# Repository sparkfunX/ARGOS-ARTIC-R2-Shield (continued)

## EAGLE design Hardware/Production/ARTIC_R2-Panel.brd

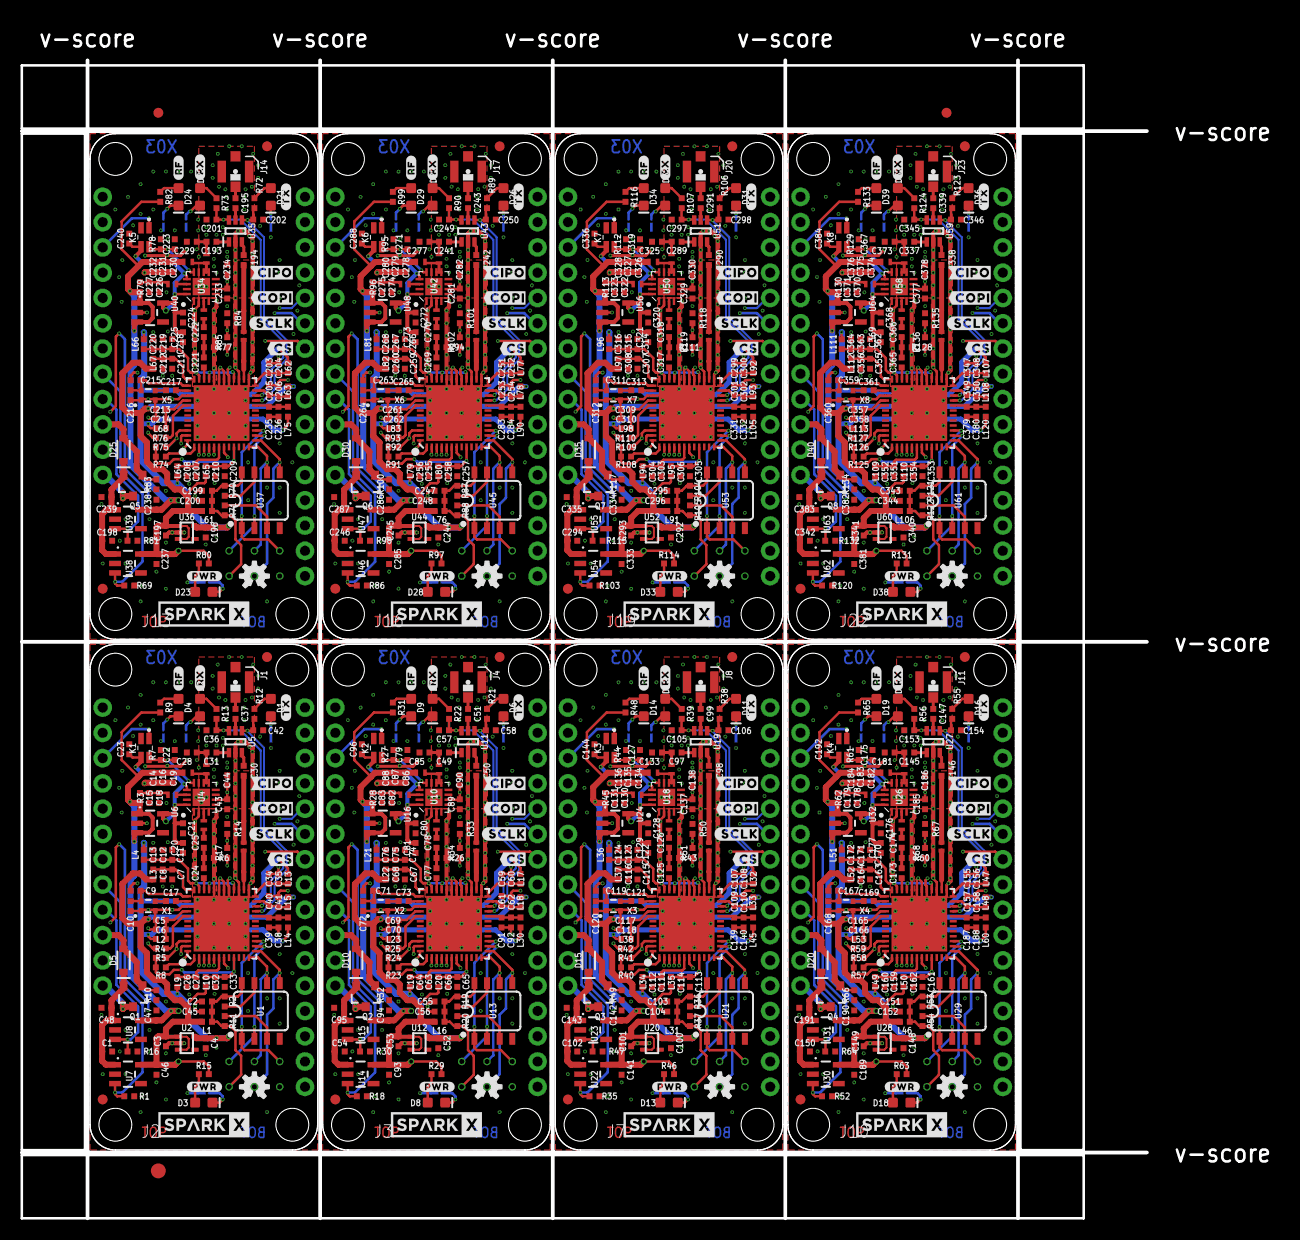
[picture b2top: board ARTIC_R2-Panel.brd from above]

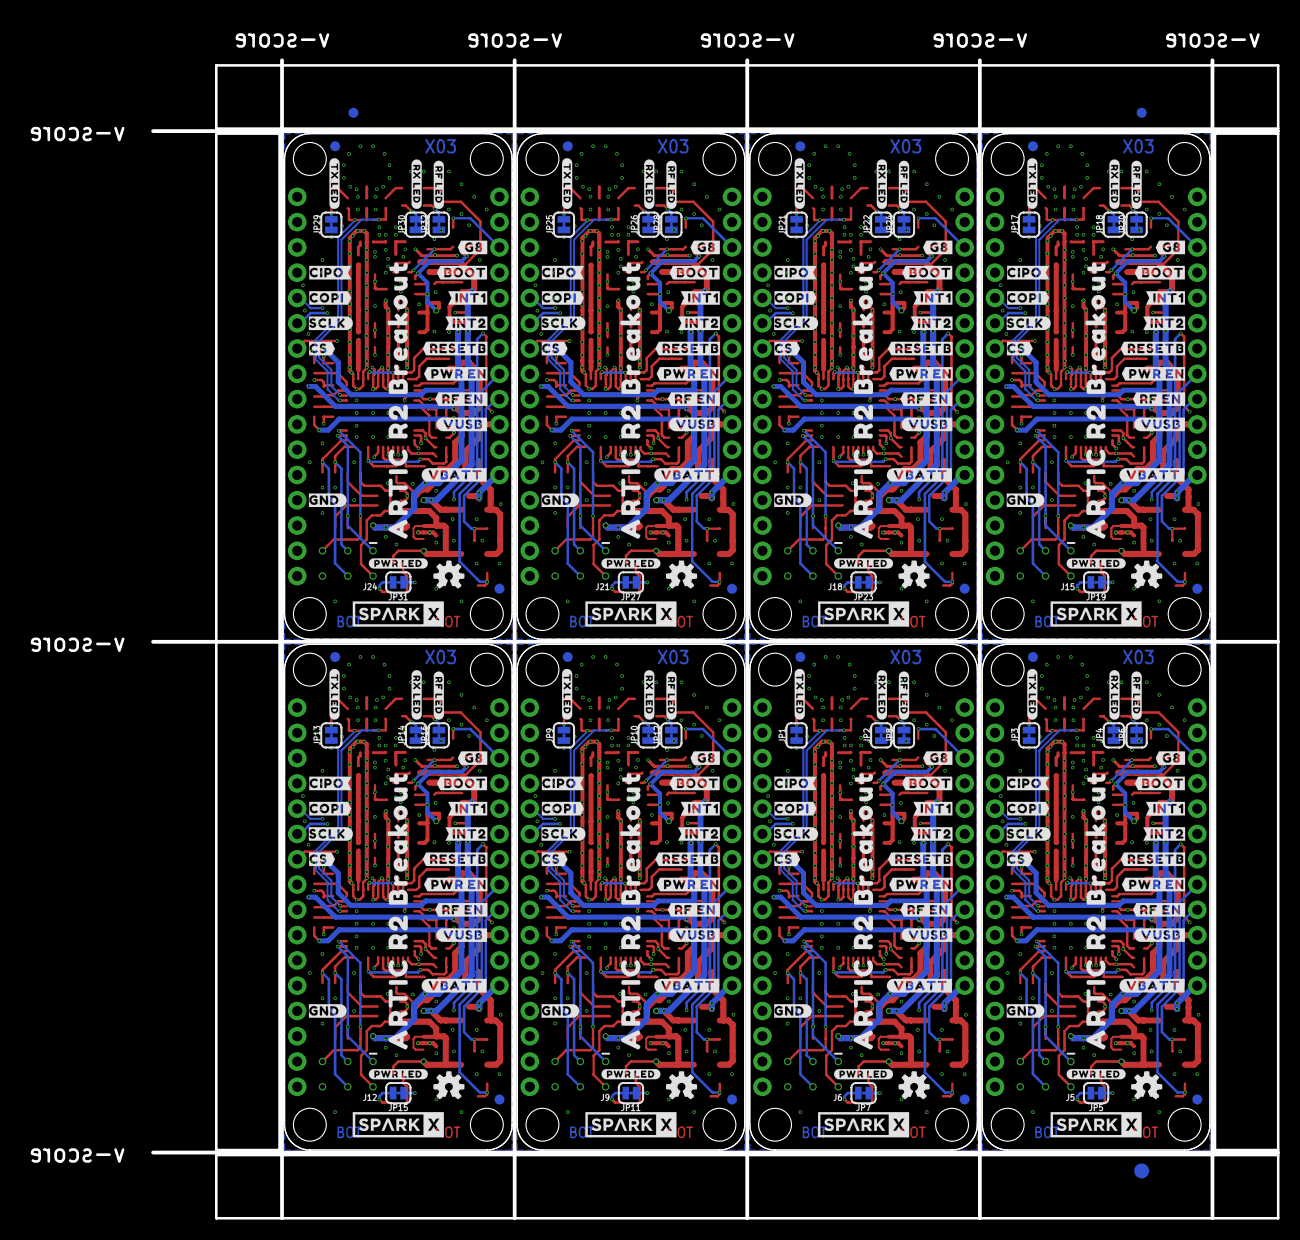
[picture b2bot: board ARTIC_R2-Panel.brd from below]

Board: 4 copper layers, 113.0 x 116.3 mm, 1142 parts (227 on the bottom side), 520 nets.

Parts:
C1, C15, C16, C20, C44, C46, C47, C54, C81, C83, C87, C90, C93, C94, C102, C129, C131, C135, C138, C141, C142, C150, C177, C179, C183, C186, C189, C190, C198, C225, C227, C231, C234, C237, C238, C246, C273, C275, C279, C282, C285, C286, C294, C321, C323, C327, C330, C333, C334, C342, C369, C371, C375, C378, C381, C382: 2.2uF; 0402-TIGHT
C2, C5, C7, C18, C27, C33, C34, C39, C40, C55, C59, C61, C63, C65, C67, C69, C82, C91, C103, C107, C109, C111, C113, C115, C117, C130, C139, C151, C155, C157, C159, C161, C163, C165, C178, C187, C199, C203, C205, C207, C209, C211, C213, C226, C235, C247, C251, C253, C255, C257, C259, C261, C274, C283, C295, C299, C301, C303, C305, C307, C309, C322, C331, C343, C347, C349, C351, C353, C355, C357, C370, C379: 22pF; 0402-TIGHT
C3, C4, C9, C12, C52, C53, C71, C75, C100, C101, C119, C123, C148, C149, C167, C171, C196, C197, C215, C219, C244, C245, C263, C267, C292, C293, C311, C315, C340, C341, C359, C363: 1.0uF; 0402-TIGHT
C6, C8, C26, C32, C35, C38, C41, C45, C48, C56, C60, C62, C64, C66, C68, C70, C92, C95, C104, C108, C110, C112, C114, C116, C118, C140, C143, C152, C156, C158, C160, C162, C164, C166, C188, C191, C200, C204, C206, C208, C210, C212, C214, C236, C239, C248, C252, C254, C256, C258, C260, C262, C284, C287, C296, C300, C302, C304, C306, C308, C310, C332, C335, C344, C348, C350, C352, C354, C356, C358, C380, C383: 0.1uF; 0402-TIGHT
C10, C72, C120, C168, C216, C264, C312, C360: 47nF; 0402-TIGHT
C11, C19, C21, C22, C23, C24, C25, C30, C31, C36, C37, C42, C43, C49, C50, C51, C57, C58, C74, C77, C78, C79, C80, C86, C89, C96, C97, C98, C99, C105, C106, C122, C125, C126, C127, C128, C134, C137, C144, C145, C146, C147, C153, C154, C170, C173, C174, C175, C176, C182, C185, C192, C193, C194, C195, C201, C202, C218, C221, C222, C223, C224, C230, C233, C240, C241, C242, C243, C249, C250, C266, C269, C270, C271, C272, C278, C281, C288, C289, C290, C291, C297, C298, C314, C317, C318, C319, C320, C326, C329, C336, C337, C338, C339, C345, C346, C362, C365, C366, C367, C368, C374, C377, C384: 100pF; 0402-TIGHT
C13, C14, C76, C88, C124, C136, C172, C184, C220, C232, C268, C280, C316, C328, C364, C376: 10uF; 0402-TIGHT
C17, C73, C121, C169, C217, C265, C313, C361: 1.0nF; 0402-TIGHT
C28, C85, C133, C181, C229, C277, C325, C373: 9.1pF; 0402-TIGHT
C29, C84, C132, C180, C228, C276, C324, C372: 2.4 pF; 0402_MURATA
D1, D2, D6, D7, D11, D12, D16, D17, D21, D22, D26, D27, D31, D32, D36, D37: Yellow; LED-0603
D3, D4, D8, D9, D13, D14, D18, D19, D23, D24, D28, D29, D33, D34, D38, D39: RED; LED-0603
D5, D10, D15, D20, D25, D30, D35, D40: 1A/23V/620mV; SOD-323
E$1, E$2, E$3, E$4: FIDUCIAL-1X2
E$5, E$6: FIDUCIAL-1.5X3
FD1, FD2, FD3, FD4, FD5, FD6, FD7, FD8, FD9, FD10, FD11, FD12, FD13, FD14, FD15, FD16, FD17, FD18, FD19, FD20, FD21, FD22, FD23, FD24, FD25, FD26, FD27, FD28, FD29, FD30, FD31, FD32: FIDUCIAL1X2; FIDUCIAL-1X2
J1, J4, J8, J11, J14, J17, J20, J23: U.FL
J2, J3, J7, J10, J13, J16, J19, J22: THING_PLUS
J5, J6, J9, J12, J15, J18, J21, J24: Flash Programming; 2X3_TEST_POINTS
JP1, JP2, JP3, JP4, JP5, JP6, JP7, JP8, JP9, JP10, JP11, JP12, JP13, JP14, JP15, JP16, JP17, JP18, JP19, JP20, JP21, JP22, JP23, JP24, JP25, JP26, JP27, JP28, JP29, JP30, JP31, JP32: JUMPER-SMT_2_NC_TRACE_SILK; SMT-JUMPER_2_NC_TRACE_SILK
K1, K2, K3, K4, K5, K6, K7, K8: TLP3475R; TLP3475RTPF
L1, L2, L3, L4, L9, L10, L13, L14, L15, L16, L17, L18, L19, L20, L21, L22, L23, L30, L31, L32, L33, L34, L35, L36, L37, L38, L45, L46, L47, L48, L49, L50, L51, L52, L53, L60, L61, L62, L63, L64, L65, L66, L67, L68, L75, L76, L77, L78, L79, L80, L81, L82, L83, L90, L91, L92, L93, L94, L95, L96, L97, L98, L105, L106, L107, L108, L109, L110, L111, L112, L113, L120: 30Ω; 0402-TIGHT
L5, L25, L40, L55, L70, L85, L100, L115: 15nH; 0402_COILCRAFT
L6, L26, L41, L56, L71, L86, L101, L116: 27nH; 0402_COILCRAFT
L7, L24, L39, L54, L69, L84, L99, L114: 18nH; 0402_COILCRAFT
L8, L27, L42, L57, L72, L87, L102, L117: 12nH; 0402_COILCRAFT
L11, L28, L43, L58, L73, L88, L103, L118: 30nH; 0402_COILCRAFT
L12, L29, L44, L59, L74, L89, L104, L119: 51nH; 0402_COILCRAFT
LOGO1, LOGO2, LOGO3, LOGO4, LOGO5, LOGO6, LOGO7, LOGO8, LOGO9, LOGO10, LOGO11, LOGO12, LOGO13, LOGO14, LOGO15, LOGO16: OSHW-LOGOS; OSHW-LOGO-S
Q1, Q2, Q3, Q4, Q5, Q6, Q7, Q8: 3.1A/30V/105mΩ; SOT23-3
R1, R7, R16, R18, R27, R30, R35, R44, R47, R52, R61, R64, R69, R78, R81, R86, R95, R98, R103, R112, R115, R120, R129, R132: 10k; 0402-TIGHT
R2, R11, R19, R20, R36, R37, R53, R54, R70, R71, R87, R88, R104, R105, R121, R122: 0; 0402-TIGHT
R3, R28, R45, R62, R79, R96, R113, R130: 3.9OHM; 0402-TIGHT
R4, R25, R42, R59, R76, R93, R110, R127: 33k; 0402-TIGHT
R5, R8, R10, R23, R24, R32, R40, R41, R49, R57, R58, R66, R74, R75, R83, R91, R92, R100, R108, R109, R117, R125, R126, R134: 100k; 0402-TIGHT
R6, R26, R43, R60, R77, R94, R111, R128: 220OHM; 0402-TIGHT
R9, R12, R13, R15, R21, R22, R29, R31, R38, R39, R46, R48, R55, R56, R63, R65, R72, R73, R80, R82, R89, R90, R97, R99, R106, R107, R114, R116, R123, R124, R131, R133: 1k; 0402-TIGHT
R14, R33, R50, R67, R84, R101, R118, R135: 470; 0402-TIGHT
R17, R34, R51, R68, R85, R102, R119, R136: 47; 0402-TIGHT
SPARKX1, SPARKX2, SPARKX3, SPARKX4, SPARKX5, SPARKX6, SPARKX7, SPARKX8, SPARKX9, SPARKX10, SPARKX11, SPARKX12, SPARKX13, SPARKX14, SPARKX15, SPARKX16: SPARKX-LOGO4; SPARKX-MEDIUM
TP1, TP2, TP3, TP4, TP5, TP6, TP7, TP8, TP9, TP10, TP11, TP12, TP13, TP14, TP15, TP16, TP17, TP18, TP19, TP20, TP21, TP22, TP23, TP24, TP25, TP26, TP27, TP28, TP29, TP30, TP31, TP32: TEST-POINTTP_15TH_THRU; TP_15TH
U1, U13, U21, U29, U37, U45, U53, U61: 2Mbit SPI Flash; SO08
U2, U12, U20, U28, U36, U44, U52, U60: 1.8V/100mA; SC70
U3, U9, U17, U25, U33, U41, U49, U57: ARTIC_R2; QFN-48
U4, U10, U18, U26, U34, U42, U50, U58: RFPA0133; QFN50P300X300X86-17N
U5, U11, U19, U27, U35, U43, U51, U59: AS179-92LF; SOT65P220X100-6N
U6, U16, U24, U32, U40, U48, U56, U64: 3.0V; SOT23-5
U7, U8, U14, U15, U22, U23, U30, U31, U38, U39, U46, U47, U54, U55, U62, U63: 3.3V; SOT23-5
U$1, U$30, U$57, U$84, U$111, U$138, U$165, U$192: #TX#0
U$2, U$31, U$58, U$85, U$112, U$139, U$166, U$193: #RX#0
U$3, U$22, U$55, U$82, U$109, U$136, U$163, U$190: #RX_LED#0
U$4, U$23, U$56, U$83, U$110, U$137, U$164, U$191: #TX_LED#0
U$5, U$49, U$76, U$103, U$130, U$157, U$184, U$211: #RF_LED#0
U$6, U$54, U$81, U$108, U$135, U$162, U$189, U$216: #G8#0
U$7, U$50, U$77, U$104, U$131, U$158, U$185, U$212: #RF#0
U$8, U$51, U$78, U$105, U$132, U$159, U$186, U$213: #RF_EN#0
U$9, U$32, U$59, U$86, U$113, U$140, U$167, U$194: CIPO#0
U$10, U$33, U$60, U$87, U$114, U$141, U$168, U$195: #CIPO0
U$11, U$34, U$61, U$88, U$115, U$142, U$169, U$196: #COPI0
U$12, U$35, U$62, U$89, U$116, U$143, U$170, U$197: COPI#0
U$13, U$36, U$63, U$90, U$117, U$144, U$171, U$198: #SCLK0
U$14, U$37, U$64, U$91, U$118, U$145, U$172, U$199: SCLK#0
U$15, U$38, U$65, U$92, U$119, U$146, U$173, U$200: #CS0
U$16, U$39, U$66, U$93, U$120, U$147, U$174, U$201: CS#0
U$17, U$43, U$70, U$97, U$124, U$151, U$178, U$205: GND#0
U$18, U$41, U$68, U$95, U$122, U$149, U$176, U$203: #RESETB0
U$19, U$42, U$69, U$96, U$123, U$150, U$177, U$204: #PWR_EN0
U$20, U$52, U$79, U$106, U$133, U$160, U$187, U$214: #VBATT#0
U$21, U$53, U$80, U$107, U$134, U$161, U$188, U$215: #VUSB#0
U$24, U$40, U$67, U$94, U$121, U$148, U$175, U$202: #BOOT0
U$25, U$45, U$72, U$99, U$126, U$153, U$180, U$207: #INT10
U$26, U$44, U$71, U$98, U$125, U$152, U$179, U$206: #INT20
U$27, U$46, U$73, U$100, U$127, U$154, U$181, U$208: #PWR_LED#0
U$28, U$47, U$74, U$101, U$128, U$155, U$182, U$209: #PWR#0
U$29, U$48, U$75, U$102, U$129, U$156, U$183, U$210: ARTIC_R2_BREAKOUT0
X1, X2, X3, X4, X5, X6, X7, X8: CRYSTAL-TCXO-26MHZ; CRYSTAL-TCXO-SMD-1.65X1.25

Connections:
1.8V: C4.1, L2.2, L4.2, L9.2, L13.2, L14.2, TP3.P$1, U2.5
1.8V1: C52.1, L17.2, L19.2, L21.2, L23.2, L30.2, TP7.P$1, U12.5
1.8V2: C100.1, L32.2, L34.2, L36.2, L38.2, L45.2, TP11.P$1, U20.5
1.8V3: C148.1, L47.2, L49.2, L51.2, L53.2, L60.2, TP15.P$1, U28.5
1.8V4: C196.1, L62.2, L64.2, L66.2, L68.2, L75.2, TP19.P$1, U36.5
1.8V5: C244.1, L77.2, L79.2, L81.2, L83.2, L90.2, TP23.P$1, U44.5
1.8V6: C292.1, L92.2, L94.2, L96.2, L98.2, L105.2, TP27.P$1, U52.5
1.8V7: C340.1, L107.2, L109.2, L111.2, L113.2, L120.2, TP31.P$1, U60.5
ANTENNA: C37.1, J1.FEED
ANTENNA1: C51.1, J4.FEED
ANTENNA2: C99.1, J8.FEED
ANTENNA3: C147.1, J11.FEED
ANTENNA4: C195.1, J14.FEED
ANTENNA5: C243.1, J17.FEED
ANTENNA6: C291.1, J20.FEED
ANTENNA7: C339.1, J23.FEED
ARTIC_PWR_EN: J2.8, R1.2, U7.3
ARTIC_PWR_EN1: J3.8, R18.2, U14.3
ARTIC_PWR_EN2: J7.8, R35.2, U22.3
ARTIC_PWR_EN3: J10.8, R52.2, U30.3
ARTIC_PWR_EN4: J13.8, R69.2, U38.3
ARTIC_PWR_EN5: J16.8, R86.2, U46.3
ARTIC_PWR_EN6: J19.8, R103.2, U54.3
ARTIC_PWR_EN7: J22.8, R120.2, U62.3
BOOT: J2.4, R5.1, U3.46
BOOT1: J3.4, R24.1, U9.46
BOOT2: J7.4, R41.1, U17.46
BOOT3: J10.4, R58.1, U25.46
BOOT4: J13.4, R75.1, U33.46
BOOT5: J16.4, R92.1, U41.46
BOOT6: J19.4, R109.1, U49.46
BOOT7: J22.4, R126.1, U57.46
CIPO: J2.16, U3.5
CIPO1: J3.16, U9.5
CIPO2: J7.16, U17.5
CIPO3: J10.16, U25.5
CIPO4: J13.16, U33.5
CIPO5: J16.16, U41.5
CIPO6: J19.16, U49.5
CIPO7: J22.16, U57.5
COPI: J2.17, U3.4
COPI1: J3.17, U9.4
COPI2: J7.17, U17.4
COPI3: J10.17, U25.4
COPI4: J13.17, U33.4
COPI5: J16.17, U41.4
COPI6: J19.17, U49.4
COPI7: J22.17, U57.4
CS: J2.19, U3.2
CS1: J3.19, U9.2
CS2: J7.19, U17.2
CS3: J10.19, U25.2
CS4: J13.19, U33.2
CS5: J16.19, U41.2
CS6: J19.19, U49.2
CS7: J22.19, U57.2
FLSH_CEN: J5.5, U1.1, U3.15
FLSH_CEN1: J6.5, U9.15, U13.1
FLSH_CEN2: J9.5, U17.15, U21.1
FLSH_CEN3: J12.5, U25.15, U29.1
FLSH_CEN4: J15.5, U33.15, U37.1
FLSH_CEN5: J18.5, U41.15, U45.1
FLSH_CEN6: J21.5, U49.15, U53.1
FLSH_CEN7: J24.5, U57.15, U61.1
FLSH_SCLK: J5.3, U1.6, U3.12
FLSH_SCLK1: J6.3, U9.12, U13.6
FLSH_SCLK2: J9.3, U17.12, U21.6
FLSH_SCLK3: J12.3, U25.12, U29.6
FLSH_SCLK4: J15.3, U33.12, U37.6
FLSH_SCLK5: J18.3, U41.12, U45.6
FLSH_SCLK6: J21.3, U49.12, U53.6
FLSH_SCLK7: J24.3, U57.12, U61.6
FLSH_SI: J5.4, U1.5, U3.13
FLSH_SI1: J6.4, U9.13, U13.5
FLSH_SI2: J9.4, U17.13, U21.5
FLSH_SI3: J12.4, U25.13, U29.5
FLSH_SI4: J15.4, U33.13, U37.5
FLSH_SI5: J18.4, U41.13, U45.5
FLSH_SI6: J21.4, U49.13, U53.5
FLSH_SI7: J24.4, U57.13, U61.5
FLSH_SO: J5.1, U1.2, U3.14
FLSH_SO1: J6.1, U9.14, U13.2
FLSH_SO2: J9.1, U17.14, U21.2
FLSH_SO3: J12.1, U25.14, U29.2
FLSH_SO4: J15.1, U33.14, U37.2
FLSH_SO5: J18.1, U41.14, U45.2
FLSH_SO6: J21.1, U49.14, U53.2
FLSH_SO7: J24.1, U57.14, U61.2
FLSH_VCC: C2.1, C45.1, J5.2, L1.1, R2.2, R11.2, U1.8
FLSH_VCC1: C55.1, C56.1, J6.2, L16.1, R19.2, R20.2, U13.8
FLSH_VCC2: C103.1, C104.1, J9.2, L31.1, R36.2, R37.2, U21.8
FLSH_VCC3: C151.1, C152.1, J12.2, L46.1, R53.2, R54.2, U29.8
FLSH_VCC4: C199.1, C200.1, J15.2, L61.1, R70.2, R71.2, U37.8
FLSH_VCC5: C247.1, C248.1, J18.2, L76.1, R87.2, R88.2, U45.8
FLSH_VCC6: C295.1, C296.1, J21.2, L91.1, R104.2, R105.2, U53.8
FLSH_VCC7: C343.1, C344.1, J24.2, L106.1, R121.2, R122.2, U61.8
G1: J3.3, K2.1
G2: J7.3, K3.1
G3: J10.3, K4.1
G4: J13.3, K5.1
G5: J16.3, K6.1
G6: J19.3, K7.1
G7: J22.3, K8.1
G8: J2.3, K1.1
GND: C1.2, C2.2, C3.2, C4.2, C5.2, C6.2, C7.2, C8.2, C9.2, C10.2, C11.2, C12.2, C13.2, C14.2, C15.2, C16.2, C18.2, C19.2, C20.1, C21.1, C22.1, C23.2, C26.2, C27.2, C28.1, C32.2, C33.2, C34.2, C35.2, C36.2, C38.2, C39.2, C40.2, C41.2, C42.2, C43.1, C44.2, C45.2, C46.2, C47.2, C48.2, J1.1, J1.2, J2.25, J5.6, JP3.1, JP4.1, JP5.1, JP6.1, K1.2, L11.P$1, L12.P$1, R1.1, R4.2, R6.1, R7.2, R10.1, R14.1, R16.1, U1.4, U2.2, U3.25, U3.27, U3.29, U3.30, U3.31, U3.32, U3.39, U3.GND, U4.2, U4.EDAP, U5.2, U6.2, U7.2, U8.2, X1.1, X1.2
GND1: C52.2, C53.2, C54.2, C55.2, C56.2, C57.2, C58.2, C59.2, C60.2, C61.2, C62.2, C63.2, C64.2, C65.2, C66.2, C67.2, C68.2, C69.2, C70.2, C71.2, C72.2, C74.2, C75.2, C76.2, C79.1, C80.1, C81.1, C82.2, C83.2, C85.1, C86.2, C87.2, C88.2, C89.1, C90.2, C91.2, C92.2, C93.2, C94.2, C95.2, C96.2, J3.25, J4.1, J4.2, J6.6, JP1.1, JP2.1, JP7.1, JP8.1, K2.2, L28.P$1, L29.P$1, R18.1, R25.2, R26.1, R27.2, R30.1, R32.1, R33.1, U9.25, U9.27, U9.29, U9.30, U9.31, U9.32, U9.39, U9.GND, U10.2, U10.EDAP, U11.2, U12.2, U13.4, U14.2, U15.2, U16.2, X2.1, X2.2
GND2: C100.2, C101.2, C102.2, C103.2, C104.2, C105.2, C106.2, C107.2, C108.2, C109.2, C110.2, C111.2, C112.2, C113.2, C114.2, C115.2, C116.2, C117.2, C118.2, C119.2, C120.2, C122.2, C123.2, C124.2, C127.1, C128.1, C129.1, C130.2, C131.2, C133.1, C134.2, C135.2, C136.2, C137.1, C138.2, C139.2, C140.2, C141.2, C142.2, C143.2, C144.2, J7.25, J8.1, J8.2, J9.6, JP9.1, JP10.1, JP11.1, JP12.1, K3.2, L43.P$1, L44.P$1, R35.1, R42.2, R43.1, R44.2, R47.1, R49.1, R50.1, U17.25, U17.27, U17.29, U17.30, U17.31, U17.32, U17.39, U17.GND, U18.2, U18.EDAP, U19.2, U20.2, U21.4, U22.2, U23.2, U24.2, X3.1, X3.2
GND3: C148.2, C149.2, C150.2, C151.2, C152.2, C153.2, C154.2, C155.2, C156.2, C157.2, C158.2, C159.2, C160.2, C161.2, C162.2, C163.2, C164.2, C165.2, C166.2, C167.2, C168.2, C170.2, C171.2, C172.2, C175.1, C176.1, C177.1, C178.2, C179.2, C181.1, C182.2, C183.2, C184.2, C185.1, C186.2, C187.2, C188.2, C189.2, C190.2, C191.2, C192.2, J10.25, J11.1, J11.2, J12.6, JP13.1, JP14.1, JP15.1, JP16.1, K4.2, L58.P$1, L59.P$1, R52.1, R59.2, R60.1, R61.2, R64.1, R66.1, R67.1, U25.25, U25.27, U25.29, U25.30, U25.31, U25.32, U25.39, U25.GND, U26.2, U26.EDAP, U27.2, U28.2, U29.4, U30.2, U31.2, U32.2, X4.1, X4.2
GND4: C196.2, C197.2, C198.2, C199.2, C200.2, C201.2, C202.2, C203.2, C204.2, C205.2, C206.2, C207.2, C208.2, C209.2, C210.2, C211.2, C212.2, C213.2, C214.2, C215.2, C216.2, C218.2, C219.2, C220.2, C223.1, C224.1, C225.1, C226.2, C227.2, C229.1, C230.2, C231.2, C232.2, C233.1, C234.2, C235.2, C236.2, C237.2, C238.2, C239.2, C240.2, J13.25, J14.1, J14.2, J15.6, JP17.1, JP18.1, JP19.1, JP20.1, K5.2, L73.P$1, L74.P$1, R69.1, R76.2, R77.1, R78.2, R81.1, R83.1, R84.1, U33.25, U33.27, U33.29, U33.30, U33.31, U33.32, U33.39, U33.GND, U34.2, U34.EDAP, U35.2, U36.2, U37.4, U38.2, U39.2, U40.2, X5.1, X5.2
GND5: C244.2, C245.2, C246.2, C247.2, C248.2, C249.2, C250.2, C251.2, C252.2, C253.2, C254.2, C255.2, C256.2, C257.2, C258.2, C259.2, C260.2, C261.2, C262.2, C263.2, C264.2, C266.2, C267.2, C268.2, C271.1, C272.1, C273.1, C274.2, C275.2, C277.1, C278.2, C279.2, C280.2, C281.1, C282.2, C283.2, C284.2, C285.2, C286.2, C287.2, C288.2, J16.25, J17.1, J17.2, J18.6, JP21.1, JP22.1, JP23.1, JP24.1, K6.2, L88.P$1, L89.P$1, R86.1, R93.2, R94.1, R95.2, R98.1, R100.1, R101.1, U41.25, U41.27, U41.29, U41.30, U41.31, U41.32, U41.39, U41.GND, U42.2, U42.EDAP, U43.2, U44.2, U45.4, U46.2, U47.2, U48.2, X6.1, X6.2
GND6: C292.2, C293.2, C294.2, C295.2, C296.2, C297.2, C298.2, C299.2, C300.2, C301.2, C302.2, C303.2, C304.2, C305.2, C306.2, C307.2, C308.2, C309.2, C310.2, C311.2, C312.2, C314.2, C315.2, C316.2, C319.1, C320.1, C321.1, C322.2, C323.2, C325.1, C326.2, C327.2, C328.2, C329.1, C330.2, C331.2, C332.2, C333.2, C334.2, C335.2, C336.2, J19.25, J20.1, J20.2, J21.6, JP25.1, JP26.1, JP27.1, JP28.1, K7.2, L103.P$1, L104.P$1, R103.1, R110.2, R111.1, R112.2, R115.1, R117.1, R118.1, U49.25, U49.27, U49.29, U49.30, U49.31, U49.32, U49.39, U49.GND, U50.2, U50.EDAP, U51.2, U52.2, U53.4, U54.2, U55.2, U56.2, X7.1, X7.2
GND7: C340.2, C341.2, C342.2, C343.2, C344.2, C345.2, C346.2, C347.2, C348.2, C349.2, C350.2, C351.2, C352.2, C353.2, C354.2, C355.2, C356.2, C357.2, C358.2, C359.2, C360.2, C362.2, C363.2, C364.2, C367.1, C368.1, C369.1, C370.2, C371.2, C373.1, C374.2, C375.2, C376.2, C377.1, C378.2, C379.2, C380.2, C381.2, C382.2, C383.2, C384.2, J22.25, J23.1, J23.2, J24.6, JP29.1, JP30.1, JP31.1, JP32.1, K8.2, L118.P$1, L119.P$1, R120.1, R127.2, R128.1, R129.2, R132.1, R134.1, R135.1, U57.25, U57.27, U57.29, U57.30, U57.31, U57.32, U57.39, U57.GND, U58.2, U58.EDAP, U59.2, U60.2, U61.4, U62.2, U63.2, U64.2, X8.1, X8.2
INT1: J2.5, U3.47
INT2: J2.6, U3.48
INT3: J3.6, U9.48
INT4: J3.5, U9.47
INT5: J7.6, U17.48
INT6: J7.5, U17.47
INT7: J10.6, U25.48
INT8: J10.5, U25.47
INT9: J13.6, U33.48
INT10: J13.5, U33.47
INT11: J16.6, U41.48
INT12: J16.5, U41.47
INT13: J19.6, U49.48
INT14: J19.5, U49.47
INT15: J22.6, U57.48
INT16: J22.5, U57.47
unnamed: C49.1, U11.1
unnamed: R2.1, U1.7
unnamed: R11.1, U1.3
unnamed: C34.1, C35.1, L13.1, U3.24
unnamed: C40.1, C41.1, L15.1, U3.23
unnamed: D2.A, R13.1
unnamed: D1.A, R12.1
unnamed: C26.1, C27.1, L9.1, U3.6
unnamed: C32.1, C33.1, L10.1, R5.2, R8.1, U3.9
unnamed: C11.1, C12.1, C13.1, L4.1, U3.28, U3.33, U3.35
unnamed: C7.1, C8.1, L3.1, U3.36
unnamed: R4.1, U3.41
unnamed: C5.1, C6.1, L2.1, U3.40
unnamed: C9.1, C10.1, U3.37, X1.4
unnamed: C17.1, X1.3
unnamed: C17.2, U3.38
unnamed: C24.1, U3.34
unnamed: C24.2, C25.1, R6.2
unnamed: L5.P$2, U4.14
unnamed: C15.1, C18.1, L5.P$1, R3.1
unnamed: C29.P$1, L11.P$2, U3.26
unnamed: D4.A, R9.1
unnamed: C50.1, U11.3
unnamed: C25.2, L7.P$1
unnamed: L7.P$2, U4.3
unnamed: L6.P$2, L8.P$1, U4.9, U4.10
unnamed: D4.C, JP6.2
unnamed: C31.1, U5.1
unnamed: C30.1, U5.3
unnamed: C37.2, U5.5
unnamed: C38.1, C39.1, L14.1, U3.20
unnamed: C51.2, U11.5
unnamed: R19.1, U13.7
unnamed: R20.1, U13.3
unnamed: D1.C, JP3.2
unnamed: D2.C, JP4.2
unnamed: D3.A, R15.1
unnamed: D3.C, JP5.2
unnamed: C59.1, C60.1, L17.1, U9.24
unnamed: C61.1, C62.1, L18.1, U9.23
unnamed: D7.A, R22.1
unnamed: D6.A, R21.1
unnamed: C63.1, C64.1, L19.1, U9.6
unnamed: C65.1, C66.1, L20.1, R23.1, R24.2, U9.9
unnamed: C74.1, C75.1, C76.1, L21.1, U9.28, U9.33, U9.35
unnamed: C67.1, C68.1, L22.1, U9.36
unnamed: R25.1, U9.41
unnamed: C69.1, C70.1, L23.1, U9.40
unnamed: C71.1, C72.1, U9.37, X2.4
unnamed: C73.1, X2.3
unnamed: C73.2, U9.38
unnamed: C77.1, U9.34
unnamed: C77.2, C78.1, R26.2
unnamed: L25.P$2, U10.14
unnamed: C82.1, C83.1, L25.P$1, R28.1
unnamed: C78.2, L24.P$1
unnamed: L24.P$2, U10.3
unnamed: L26.P$2, L27.P$1, U10.9, U10.10
unnamed: C84.P$1, L28.P$2, U9.26
unnamed: C91.1, C92.1, L30.1, U9.20
unnamed: D6.C, JP1.2
unnamed: D7.C, JP2.2
unnamed: D8.A, R29.1
unnamed: D8.C, JP7.2
unnamed: D9.A, R31.1
unnamed: D9.C, JP8.2
unnamed: C97.1, U19.1
unnamed: C98.1, U19.3
unnamed: C99.2, U19.5
unnamed: R36.1, U21.7
unnamed: R37.1, U21.3
unnamed: C107.1, C108.1, L32.1, U17.24
unnamed: C109.1, C110.1, L33.1, U17.23
unnamed: D12.A, R39.1
unnamed: D11.A, R38.1
unnamed: C111.1, C112.1, L34.1, U17.6
unnamed: C113.1, C114.1, L35.1, R40.1, R41.2, U17.9
unnamed: C122.1, C123.1, C124.1, L36.1, U17.28, U17.33, U17.35
unnamed: C115.1, C116.1, L37.1, U17.36
unnamed: R42.1, U17.41
unnamed: C117.1, C118.1, L38.1, U17.40
unnamed: C119.1, C120.1, U17.37, X3.4
unnamed: C121.1, X3.3
unnamed: C121.2, U17.38
unnamed: C125.1, U17.34
unnamed: C125.2, C126.1, R43.2
unnamed: L40.P$2, U18.14
unnamed: C130.1, C131.1, L40.P$1, R45.1
unnamed: C126.2, L39.P$1
unnamed: L39.P$2, U18.3
unnamed: L41.P$2, L42.P$1, U18.9, U18.10
unnamed: C132.P$1, L43.P$2, U17.26
unnamed: C139.1, C140.1, L45.1, U17.20
unnamed: D11.C, JP9.2
unnamed: D12.C, JP10.2
unnamed: D13.A, R46.1
unnamed: D13.C, JP11.2
unnamed: D14.A, R48.1
unnamed: D14.C, JP12.2
unnamed: C145.1, U27.1
unnamed: C146.1, U27.3
unnamed: C147.2, U27.5
unnamed: R53.1, U29.7
unnamed: R54.1, U29.3
unnamed: C155.1, C156.1, L47.1, U25.24
unnamed: C157.1, C158.1, L48.1, U25.23
unnamed: D17.A, R56.1
unnamed: D16.A, R55.1
unnamed: C159.1, C160.1, L49.1, U25.6
unnamed: C161.1, C162.1, L50.1, R57.1, R58.2, U25.9
unnamed: C170.1, C171.1, C172.1, L51.1, U25.28, U25.33, U25.35
unnamed: C163.1, C164.1, L52.1, U25.36
unnamed: R59.1, U25.41
unnamed: C165.1, C166.1, L53.1, U25.40
unnamed: C167.1, C168.1, U25.37, X4.4
unnamed: C169.1, X4.3
unnamed: C169.2, U25.38
unnamed: C173.1, U25.34
unnamed: C173.2, C174.1, R60.2
unnamed: L55.P$2, U26.14
unnamed: C178.1, C179.1, L55.P$1, R62.1
unnamed: C174.2, L54.P$1
unnamed: L54.P$2, U26.3
unnamed: L56.P$2, L57.P$1, U26.9, U26.10
unnamed: C180.P$1, L58.P$2, U25.26
unnamed: C187.1, C188.1, L60.1, U25.20
unnamed: D16.C, JP13.2
unnamed: D17.C, JP14.2
unnamed: D18.A, R63.1
unnamed: D18.C, JP15.2
unnamed: D19.A, R65.1
unnamed: D19.C, JP16.2
unnamed: C193.1, U35.1
unnamed: C194.1, U35.3
unnamed: C195.2, U35.5
unnamed: R70.1, U37.7
unnamed: R71.1, U37.3
unnamed: C203.1, C204.1, L62.1, U33.24
unnamed: C205.1, C206.1, L63.1, U33.23
unnamed: D22.A, R73.1
unnamed: D21.A, R72.1
unnamed: C207.1, C208.1, L64.1, U33.6
unnamed: C209.1, C210.1, L65.1, R74.1, R75.2, U33.9
unnamed: C218.1, C219.1, C220.1, L66.1, U33.28, U33.33, U33.35
unnamed: C211.1, C212.1, L67.1, U33.36
unnamed: R76.1, U33.41
unnamed: C213.1, C214.1, L68.1, U33.40
unnamed: C215.1, C216.1, U33.37, X5.4
unnamed: C217.1, X5.3
unnamed: C217.2, U33.38
unnamed: C221.1, U33.34
unnamed: C221.2, C222.1, R77.2
unnamed: L70.P$2, U34.14
unnamed: C226.1, C227.1, L70.P$1, R79.1
unnamed: C222.2, L69.P$1
unnamed: L69.P$2, U34.3
unnamed: L71.P$2, L72.P$1, U34.9, U34.10
unnamed: C228.P$1, L73.P$2, U33.26
unnamed: C235.1, C236.1, L75.1, U33.20
unnamed: D21.C, JP17.2
unnamed: D22.C, JP18.2
unnamed: D23.A, R80.1
unnamed: D23.C, JP19.2
unnamed: D24.A, R82.1
unnamed: D24.C, JP20.2
unnamed: C241.1, U43.1
unnamed: C242.1, U43.3
unnamed: C243.2, U43.5
unnamed: R87.1, U45.7
unnamed: R88.1, U45.3
unnamed: C251.1, C252.1, L77.1, U41.24
unnamed: C253.1, C254.1, L78.1, U41.23
unnamed: D27.A, R90.1
unnamed: D26.A, R89.1
unnamed: C255.1, C256.1, L79.1, U41.6
unnamed: C257.1, C258.1, L80.1, R91.1, R92.2, U41.9
unnamed: C266.1, C267.1, C268.1, L81.1, U41.28, U41.33, U41.35
unnamed: C259.1, C260.1, L82.1, U41.36
unnamed: R93.1, U41.41
unnamed: C261.1, C262.1, L83.1, U41.40
unnamed: C263.1, C264.1, U41.37, X6.4
unnamed: C265.1, X6.3
unnamed: C265.2, U41.38
unnamed: C269.1, U41.34
unnamed: C269.2, C270.1, R94.2
unnamed: L85.P$2, U42.14
unnamed: C274.1, C275.1, L85.P$1, R96.1
unnamed: C270.2, L84.P$1
unnamed: L84.P$2, U42.3
unnamed: L86.P$2, L87.P$1, U42.9, U42.10
unnamed: C276.P$1, L88.P$2, U41.26
unnamed: C283.1, C284.1, L90.1, U41.20
unnamed: D26.C, JP21.2
unnamed: D27.C, JP22.2
unnamed: D28.A, R97.1
unnamed: D28.C, JP23.2
unnamed: D29.A, R99.1
unnamed: D29.C, JP24.2
unnamed: C289.1, U51.1
unnamed: C290.1, U51.3
unnamed: C291.2, U51.5
unnamed: R104.1, U53.7
unnamed: R105.1, U53.3
unnamed: C299.1, C300.1, L92.1, U49.24
unnamed: C301.1, C302.1, L93.1, U49.23
unnamed: D32.A, R107.1
unnamed: D31.A, R106.1
unnamed: C303.1, C304.1, L94.1, U49.6
unnamed: C305.1, C306.1, L95.1, R108.1, R109.2, U49.9
unnamed: C314.1, C315.1, C316.1, L96.1, U49.28, U49.33, U49.35
unnamed: C307.1, C308.1, L97.1, U49.36
unnamed: R110.1, U49.41
unnamed: C309.1, C310.1, L98.1, U49.40
unnamed: C311.1, C312.1, U49.37, X7.4
unnamed: C313.1, X7.3
unnamed: C313.2, U49.38
unnamed: C317.1, U49.34
unnamed: C317.2, C318.1, R111.2
unnamed: L100.P$2, U50.14
unnamed: C322.1, C323.1, L100.P$1, R113.1
unnamed: C318.2, L99.P$1
unnamed: L99.P$2, U50.3
unnamed: L101.P$2, L102.P$1, U50.9, U50.10
unnamed: C324.P$1, L103.P$2, U49.26
unnamed: C331.1, C332.1, L105.1, U49.20
unnamed: D31.C, JP25.2
unnamed: D32.C, JP26.2
unnamed: D33.A, R114.1
unnamed: D33.C, JP27.2
unnamed: D34.A, R116.1
unnamed: D34.C, JP28.2
unnamed: C337.1, U59.1
unnamed: C338.1, U59.3
unnamed: C339.2, U59.5
unnamed: R121.1, U61.7
unnamed: R122.1, U61.3
unnamed: C347.1, C348.1, L107.1, U57.24
unnamed: C349.1, C350.1, L108.1, U57.23
unnamed: D37.A, R124.1
unnamed: D36.A, R123.1
unnamed: C351.1, C352.1, L109.1, U57.6
unnamed: C353.1, C354.1, L110.1, R125.1, R126.2, U57.9
unnamed: C362.1, C363.1, C364.1, L111.1, U57.28, U57.33, U57.35
unnamed: C355.1, C356.1, L112.1, U57.36
unnamed: R127.1, U57.41
unnamed: C357.1, C358.1, L113.1, U57.40
unnamed: C359.1, C360.1, U57.37, X8.4
unnamed: C361.1, X8.3
unnamed: C361.2, U57.38
unnamed: C365.1, U57.34
unnamed: C365.2, C366.1, R128.2
unnamed: L115.P$2, U58.14
unnamed: C370.1, C371.1, L115.P$1, R130.1
unnamed: C366.2, L114.P$1
unnamed: L114.P$2, U58.3
unnamed: L116.P$2, L117.P$1, U58.9, U58.10
unnamed: C372.P$1, L118.P$2, U57.26
unnamed: C379.1, C380.1, L120.1, U57.20
unnamed: D36.C, JP29.2
unnamed: D37.C, JP30.2
unnamed: D38.A, R131.1
unnamed: D38.C, JP31.2
unnamed: D39.A, R133.1
unnamed: D39.C, JP32.2
PA_PD: R17.1, U3.7
PA_PD1: R34.1, U9.7
PA_PD2: R51.1, U17.7
PA_PD3: R68.1, U25.7
PA_PD4: R85.1, U33.7
PA_PD5: R102.1, U41.7
PA_PD6: R119.1, U49.7
PA_PD7: R136.1, U57.7
PD: C43.2, C44.1, R14.2, R17.2, U4.6
PD1: C89.2, C90.1, R33.2, R34.2, U10.6
PD2: C137.2, C138.1, R50.2, R51.2, U18.6
PD3: C185.2, C186.1, R67.2, R68.2, U26.6
PD4: C233.2, C234.1, R84.2, R85.2, U34.6
PD5: C281.2, C282.1, R101.2, R102.2, U42.6
PD6: C329.2, C330.1, R118.2, R119.2, U50.6
PD7: C377.2, C378.1, R135.2, R136.2, U58.6
RESETB: J2.7, R8.2, U3.1
RESETB1: J3.7, R23.2, U9.1
RESETB2: J7.7, R40.2, U17.1
RESETB3: J10.7, R57.2, U25.1
RESETB4: J13.7, R74.2, U33.1
RESETB5: J16.7, R91.2, U41.1
RESETB6: J19.7, R108.2, U49.1
RESETB7: J22.7, R125.2, U57.1
RFG1: C79.2, K2.4, R27.1, U10.12
RFG2: C127.2, K3.4, R44.1, U18.12
RFG3: C175.2, K4.4, R61.1, U26.12
RFG4: C223.2, K5.4, R78.1, U34.12
RFG5: C271.2, K6.4, R95.1, U42.12
RFG6: C319.2, K7.4, R112.1, U50.12
RFG7: C367.2, K8.4, R129.1, U58.12
RFG8: C22.2, K1.4, R7.1, U4.12
RF_PWR_EN: J2.9, R16.2, U8.3
RF_PWR_EN1: J3.9, R30.2, U15.3
RF_PWR_EN2: J7.9, R47.2, U23.3
RF_PWR_EN3: J10.9, R64.2, U31.3
RF_PWR_EN4: J13.9, R81.2, U39.3
RF_PWR_EN5: J16.9, R98.2, U47.3
RF_PWR_EN6: J19.9, R115.2, U55.3
RF_PWR_EN7: J22.9, R132.2, U63.3
RF_RX: C29.P$2, C30.2, L12.P$2
RF_RX1: C50.2, C84.P$2, L29.P$2
RF_RX2: C98.2, C132.P$2, L44.P$2
RF_RX3: C146.2, C180.P$2, L59.P$2
RF_RX4: C194.2, C228.P$2, L74.P$2
RF_RX5: C242.2, C276.P$2, L89.P$2
RF_RX6: C290.2, C324.P$2, L104.P$2
RF_RX7: C338.2, C372.P$2, L119.P$2
RF_TX: C28.2, C31.2, L8.P$2
RF_TX1: C49.2, C85.2, L27.P$2
RF_TX2: C97.2, C133.2, L42.P$2
RF_TX3: C145.2, C181.2, L57.P$2
RF_TX4: C193.2, C229.2, L72.P$2
RF_TX5: C241.2, C277.2, L87.P$2
RF_TX6: C289.2, C325.2, L102.P$2
RF_TX7: C337.2, C373.2, L117.P$2
RXSW: C36.1, R13.2, U3.22, U5.6
RXSW1: C57.1, R22.2, U9.22, U11.6
RXSW2: C105.1, R39.2, U17.22, U19.6
RXSW3: C153.1, R56.2, U25.22, U27.6
RXSW4: C201.1, R73.2, U33.22, U35.6
RXSW5: C249.1, R90.2, U41.22, U43.6
RXSW6: C297.1, R107.2, U49.22, U51.6
RXSW7: C345.1, R124.2, U57.22, U59.6
SCLK: J2.18, U3.3
SCLK1: J3.18, U9.3
SCLK2: J7.18, U17.3
SCLK3: J10.18, U25.3
SCLK4: J13.18, U33.3
SCLK5: J16.18, U41.3
SCLK6: J19.18, U49.3
SCLK7: J22.18, U57.3
TXSW: C42.1, R12.2, U3.21, U5.4
TXSW1: C58.1, R21.2, U9.21, U11.4
TXSW2: C106.1, R38.2, U17.21, U19.4
TXSW3: C154.1, R55.2, U25.21, U27.4
TXSW4: C202.1, R72.2, U33.21, U35.4
TXSW5: C250.1, R89.2, U41.21, U43.4
TXSW6: C298.1, R106.2, U49.21, U51.4
TXSW7: C346.1, R123.2, U57.21, U59.4
VDD: C3.1, C46.1, L1.2, L3.2, L10.2, L15.2, R15.2, TP1.P$1, U2.1, U2.3, U7.5
VDD1: C53.1, C93.1, L16.2, L18.2, L20.2, L22.2, R29.2, TP5.P$1, U12.1, U12.3, U14.5
VDD2: C101.1, C141.1, L31.2, L33.2, L35.2, L37.2, R46.2, TP9.P$1, U20.1, U20.3, U22.5
VDD3: C149.1, C189.1, L46.2, L48.2, L50.2, L52.2, R63.2, TP13.P$1, U28.1, U28.3, U30.5
VDD4: C197.1, C237.1, L61.2, L63.2, L65.2, L67.2, R80.2, TP17.P$1, U36.1, U36.3, U38.5
VDD5: C245.1, C285.1, L76.2, L78.2, L80.2, L82.2, R97.2, TP21.P$1, U44.1, U44.3, U46.5
VDD6: C293.1, C333.1, L91.2, L93.2, L95.2, L97.2, R114.2, TP25.P$1, U52.1, U52.3, U54.5
VDD7: C341.1, C381.1, L106.2, L108.2, L110.2, L112.2, R131.2, TP29.P$1, U60.1, U60.3, U62.5
VDDA: C14.1, C16.1, C19.1, C47.1, L6.P$1, R3.2, R9.2, TP2.P$1, U6.1, U6.3, U8.5
VDDA1: C86.1, C87.1, C88.1, C94.1, L26.P$1, R28.2, R31.2, TP6.P$1, U15.5, U16.1, U16.3
VDDA2: C134.1, C135.1, C136.1, C142.1, L41.P$1, R45.2, R48.2, TP10.P$1, U23.5, U24.1, U24.3
VDDA3: C182.1, C183.1, C184.1, C190.1, L56.P$1, R62.2, R65.2, TP14.P$1, U31.5, U32.1, U32.3
VDDA4: C230.1, C231.1, C232.1, C238.1, L71.P$1, R79.2, R82.2, TP18.P$1, U39.5, U40.1, U40.3
VDDA5: C278.1, C279.1, C280.1, C286.1, L86.P$1, R96.2, R99.2, TP22.P$1, U47.5, U48.1, U48.3
VDDA6: C326.1, C327.1, C328.1, C334.1, L101.P$1, R113.2, R116.2, TP26.P$1, U55.5, U56.1, U56.3
VDDA7: C374.1, C375.1, C376.1, C382.1, L116.P$1, R130.2, R133.2, TP30.P$1, U63.5, U64.1, U64.3
VIN: C1.1, C48.1, D5.C, Q1.2, U7.1, U8.1
VIN1: C54.1, C95.1, D10.C, Q2.2, U14.1, U15.1
VIN2: C102.1, C143.1, D15.C, Q3.2, U22.1, U23.1
VIN3: C150.1, C191.1, D20.C, Q4.2, U30.1, U31.1
VIN4: C198.1, C239.1, D25.C, Q5.2, U38.1, U39.1
VIN5: C246.1, C287.1, D30.C, Q6.2, U46.1, U47.1
VIN6: C294.1, C335.1, D35.C, Q7.2, U54.1, U55.1
VIN7: C342.1, C383.1, D40.C, Q8.2, U62.1, U63.1
VREF1: C20.2, C21.2, C23.1, K1.3, TP4.P$1, U4.13, U4.16, U6.5
VREF2: C80.2, C81.2, C96.1, K2.3, TP8.P$1, U10.13, U10.16, U16.5
VREF3: C128.2, C129.2, C144.1, K3.3, TP12.P$1, U18.13, U18.16, U24.5
VREF4: C176.2, C177.2, C192.1, K4.3, TP16.P$1, U26.13, U26.16, U32.5
VREF5: C224.2, C225.2, C240.1, K5.3, TP20.P$1, U34.13, U34.16, U40.5
VREF6: C272.2, C273.2, C288.1, K6.3, TP24.P$1, U42.13, U42.16, U48.5
VREF7: C320.2, C321.2, C336.1, K7.3, TP28.P$1, U50.13, U50.16, U56.5
VREF8: C368.2, C369.2, C384.1, K8.3, TP32.P$1, U58.13, U58.16, U64.5
V_BATT: J2.12, Q1.3
V_BATT1: J3.12, Q2.3
V_BATT2: J7.12, Q3.3
V_BATT3: J10.12, Q4.3
V_BATT4: J13.12, Q5.3
V_BATT5: J16.12, Q6.3
V_BATT6: J19.12, Q7.3
V_BATT7: J22.12, Q8.3
V_USB: D5.A, J2.10, Q1.1, R10.2
V_USB1: D10.A, J3.10, Q2.1, R32.2
V_USB2: D15.A, J7.10, Q3.1, R49.2
V_USB3: D20.A, J10.10, Q4.1, R66.2
V_USB4: D25.A, J13.10, Q5.1, R83.2
V_USB5: D30.A, J16.10, Q6.1, R100.2
V_USB6: D35.A, J19.10, Q7.1, R117.2
V_USB7: D40.A, J22.10, Q8.1, R134.2

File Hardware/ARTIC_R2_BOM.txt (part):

Part    Value                         Device                          Package                    Description                                                         DESCRIPTION                                              DESIGNER DIGIKEY_PART                      MANUFACTURER MANUFACTURER_NAME MANUFACTURER_PART_NUMBER MANU_PART               MOUSER_PART          MOUSER_PART_NUMBER MOUSER_PRICE-STOCK                                                PACKAGE   PROD_ID     REV SF_ID     VALUE          
C1      2.2uF                         2.2UF-0402_TIGHT-10V-10%-X5R    0402-TIGHT                 2.2µF ceramic capacitors                                                                                                                                                                                                                                                                                                                                                    CAP-14232                 2.2uF          
C2      22pF                          22PF-0402T-16V-10%              0402-TIGHT                 22pF ceramic capacitors                                                                                                                                                                                                                                                                                                                                                     CAP-14674                 22pF           
C3      1.0uF                         1.0UF-0402T-16V-10%             0402-TIGHT                 1µF ceramic capacitors                                                                                                                                                                                                                                                                                                                                                      CAP-12417                 1.0uF          
C4      1.0uF                         1.0UF-0402T-16V-10%             0402-TIGHT                 1µF ceramic capacitors                                                                                                                                                                                                                                                                                                                                                      CAP-12417                 1.0uF          
C5      22pF                          22PF-0402T-16V-10%              0402-TIGHT                 22pF ceramic capacitors                                                                                                                                                                                                                                                                                                                                                     CAP-14674                 22pF           
C6      0.1uF                         0.1UF-0402T-6.3V-10%-X7R        0402-TIGHT                 0.1µF ceramic capacitors                                                                                                                                                                                                                                                                                                                                                    CAP-14993                 0.1uF          
C7      22pF                          22PF-0402T-16V-10%              0402-TIGHT                 22pF ceramic capacitors                                                                                                                                                                                                                                                                                                                                                     CAP-14674                 22pF           
C8      0.1uF                         0.1UF-0402T-6.3V-10%-X7R        0402-TIGHT                 0.1µF ceramic capacitors                                                                                                                                                                                                                                                                                                                                                    CAP-14993                 0.1uF          
C9      1.0uF                         1.0UF-0402T-16V-10%             0402-TIGHT                 1µF ceramic capacitors                                                                                                                                                                                                                                                                                                                                                      CAP-12417                 1.0uF          
C10     47nF                          47NF-0402_TIGHT-25V-10%-X7R     0402-TIGHT                 47nF ceramic capacitors                                                                                                                                                                                                                                                                                                                                                     CAP-14243                 47nF           
C11     100pF                         100PF-0402T-50V-5%              0402-TIGHT                 100pF/0.1nF ceramic capacitors                                                                                                                                                                                                                                                                                                                                              CAP-13458                 100pF          
C12     1.0uF                         1.0UF-0402T-16V-10%             0402-TIGHT                 1µF ceramic capacitors                                                                                                                                                                                                                                                                                                                                                      CAP-12417                 1.0uF          
C13     10uF                          10UF-0402T-6.3V-20%             0402-TIGHT                 10.0µF ceramic capacitors                                                                                                                                                                                                                                                                                                                                                   CAP-14848                 10uF           
C14     10uF                          10UF-0402T-6.3V-20%             0402-TIGHT                 10.0µF ceramic capacitors                                                                                                                                                                                                                                                                                                                                                   CAP-14848                 10uF           
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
